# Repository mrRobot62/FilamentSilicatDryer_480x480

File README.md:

# ESP32-S3 Filament & SilicaGel Dryer UI

> English documentation is available in [README_EN.md](README_EN.md).
> Diese README ist die deutsche Hauptfassung.

## Management Summary

> [!NOTE]
>
> Große Teile der Dokumentation basieren auf aktuellen Source-Code-Ständen, Analysen und Reverse-Engineering.
> Die Formulierungen wurden zu wesentlichen Teilen KI-gestützt ausgearbeitet und werden schrittweise technisch nachgeschärft.

Technische Grundlage:

- `HOST`: ESP32-S3 mit 480x480-Touchdisplay und LVGL
- `CLIENT`: ESP32-WROOM für Aktorik, Telemetrie und Safety-Gating
- Kommunikation: UART/TTL mit ASCII-Protokoll
- Temperaturmessung: externer Thermofühler plus clientseitige Sensorik

Der Filament- und SilicaGel-Dryer ersetzt die originale Bedien- und Steuerlogik eines Mini-Backofens durch eine transparente Zwei-Controller-Architektur. Ziel ist kein kosmetischer Umbau, sondern ein nachvollziehbares, wartbares und erweiterbares Trocknungssystem für Filament und Silicagel.

## Aktueller Release-Stand

- Version: `0.7.3`
- Fokus:
  - konfigurierbarer Parameterscreen auf dem `HOST`
  - NVM-persistente Fast-Shortcuts
  - konfigurierbare Heater-Curve-Presets
  - Display-Timeout mit Dimmung und Wake-on-Touch-Schutz
  - hostseitige Langzeit-CSV-Aggregation `CSV_LR_HOST`
  - erweiterte aktive Hardware-, Wiring- und BOM-Baseline in der Doku

## Kritische Sicherheitsregel

> [!WARNING]
>
> **USB darf nicht angeschlossen werden, waehrend das Geraet am 230-V-Netz betrieben wird.**
> Durch netzseitige Bezuege des wiederverwendeten Powerboards koennen gefaehrliche Potentialunterschiede entstehen.

Erlaubte Varianten:

- Netzstecker ziehen, bevor USB verbunden wird
- USB-Isolator verwenden
- galvanisch getrennte Versorgung / isoliertes Setup verwenden

Die gepflegte Fassung dieser Regeln liegt in [doc/03_user_guide/01_installation_and_safety.md](doc/03_user_guide/01_installation_and_safety.md).

## Dokumentationsstatus

Aktiv gepflegt:

- Hardware- und Reverse-Engineering-Grundlagen
- Softwarearchitektur fuer `HOST`, `CLIENT` und Kommunikation
- Installations- und Sicherheitsbasis
- Bedienkonzept und Screen-Ueberblick
- Release- und Update-Baseline

Noch im Ausbau:

- vollstaendige Wiring-Dokumentation
- BOM mit Varianten
- Test- und Validierungsnachweise
- bebilderte Installationsschritte

## Einstieg

- Dokumentationsindex: [doc/README.md](doc/README.md)
- Hardware: [doc/01_reverse_engineering_and_hardware/README.md](doc/01_reverse_engineering_and_hardware/README.md)
- Hardware-Setup: [doc/01_reverse_engineering_and_hardware/04_hardware_setup.md](doc/01_reverse_engineering_and_hardware/04_hardware_setup.md)
- Wiring-Baseline: [doc/01_reverse_engineering_and_hardware/05_wiring_baseline.md](doc/01_reverse_engineering_and_hardware/05_wiring_baseline.md)
- BOM-Baseline: [doc/01_reverse_engineering_and_hardware/06_bom_baseline.md](doc/01_reverse_engineering_and_hardware/06_bom_baseline.md)
- Softwarearchitektur: [doc/02_software_architecture/README.md](doc/02_software_architecture/README.md)
- User Guide: [doc/03_user_guide/README.md](doc/03_user_guide/README.md)
- Installation und Sicherheit: [doc/03_user_guide/01_installation_and_safety.md](doc/03_user_guide/01_installation_and_safety.md)
- Betrieb und Screens: [doc/03_user_guide/02_operation_and_screens.md](doc/03_user_guide/02_operation_and_screens.md)
- Release und Update: [doc/03_user_guide/03_release_and_update.md](doc/03_user_guide/03_release_and_update.md)

## Referenzplattform

Aktuelle Basis:

- EMPHSISM AFTO-1505D Mini-Backofen / Airfryer
- reverse-engineertes Powerboard wird weiterverwendet
- Original-UI wird durch `HOST` und `CLIENT` ersetzt

Die aktive Hardware-Dokumentation liegt unter [doc/01_reverse_engineering_and_hardware/README.md](doc/01_reverse_engineering_and_hardware/README.md).

## Systemarchitektur

Zentrales Prinzip: `Oven Runtime State` als Single Source of Truth.

```mermaid
flowchart LR

  subgraph UX["UX Controller (ESP32 S3)"]
    S3["ESP32 S3 MCU"]
    TFT["480x480 Touch Display"]
    TOUCH["Touch Controller"]
    IO["GPIO Outputs"]
  end

  subgraph CLIENT["IO Controller (ESP32 WROOM)"]
    WROOM["ESP32 WROOM MCU"]
    UART2["UART TTL Interface"]
    OUT["Output Mask"]
    IN["Status Inputs"]
  end

  subgraph PWR["Powerboard (Reverse Engineered)"]
    PB["Powerboard Logic"]
    REL["Relays and Power Drivers"]
    SNS["Door and Safety Signals"]
  end

  subgraph SENS["External Temperature Sensor"]
    TC["Temperature Sensor"]
    AMP["Sensor Interface"]
  end

  S3 -->|"SPI or RGB"| TFT
  S3 -->|"I2C or SPI"| TOUCH
  S3 <-->|"UART TTL"| UART2
  UART2 <-->|"Serial Link"| WROOM
  WROOM -->|"Control Lines"| OUT
  OUT --> PB
  PB --> REL
  PB -->|"Status Bits"| IN
  IN --> WROOM
  TC --> AMP
  AMP --> S3
```

Die detaillierte Architektur ist unter [doc/02_software_architecture/README.md](doc/02_software_architecture/README.md) beschrieben.

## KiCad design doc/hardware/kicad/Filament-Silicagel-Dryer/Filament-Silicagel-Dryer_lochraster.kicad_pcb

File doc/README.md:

# Documentation

This folder reflects the active documentation baseline on top of release `v0.7.3`.

The active documentation is intentionally reduced to three maintained sections:

1. [Reverse Engineering and Hardware](01_reverse_engineering_and_hardware/README.md)
2. [Software Architecture](02_software_architecture/README.md)
3. [User Guide](03_user_guide/README.md)

Legacy material is still available in the archive:

- [Archive snapshot before the reorganization](archive/pre_reorg_v0.7.1/README.md)

## Scope of the active documentation

The new structure reflects the current product split:

- `HOST`: ESP32-S3 UI controller with LVGL, runtime state, parameter storage and communication control
- `CLIENT`: ESP32-WROOM hardware controller for outputs, telemetry and safety gating
- Reverse-engineered oven power board reused as actuator and supply stage

## Recommended next additions

The active structure now covers the current architecture, user operation, installation baseline and release/update baseline.

The next useful additions should be:

- a dedicated manufacturing and wiring guide
- a test and validation section
- a BOM with validated hardware variants
- an explicit safety concept and validation chapter

## Phase-2 hardware documentation status

The active hardware section now also includes:

- a hardware setup baseline
- a wiring baseline
- a BOM baseline

These pages intentionally establish the maintained structure first. They should be refined with real photos, exact connector mappings and validated part numbers in the next iterations.

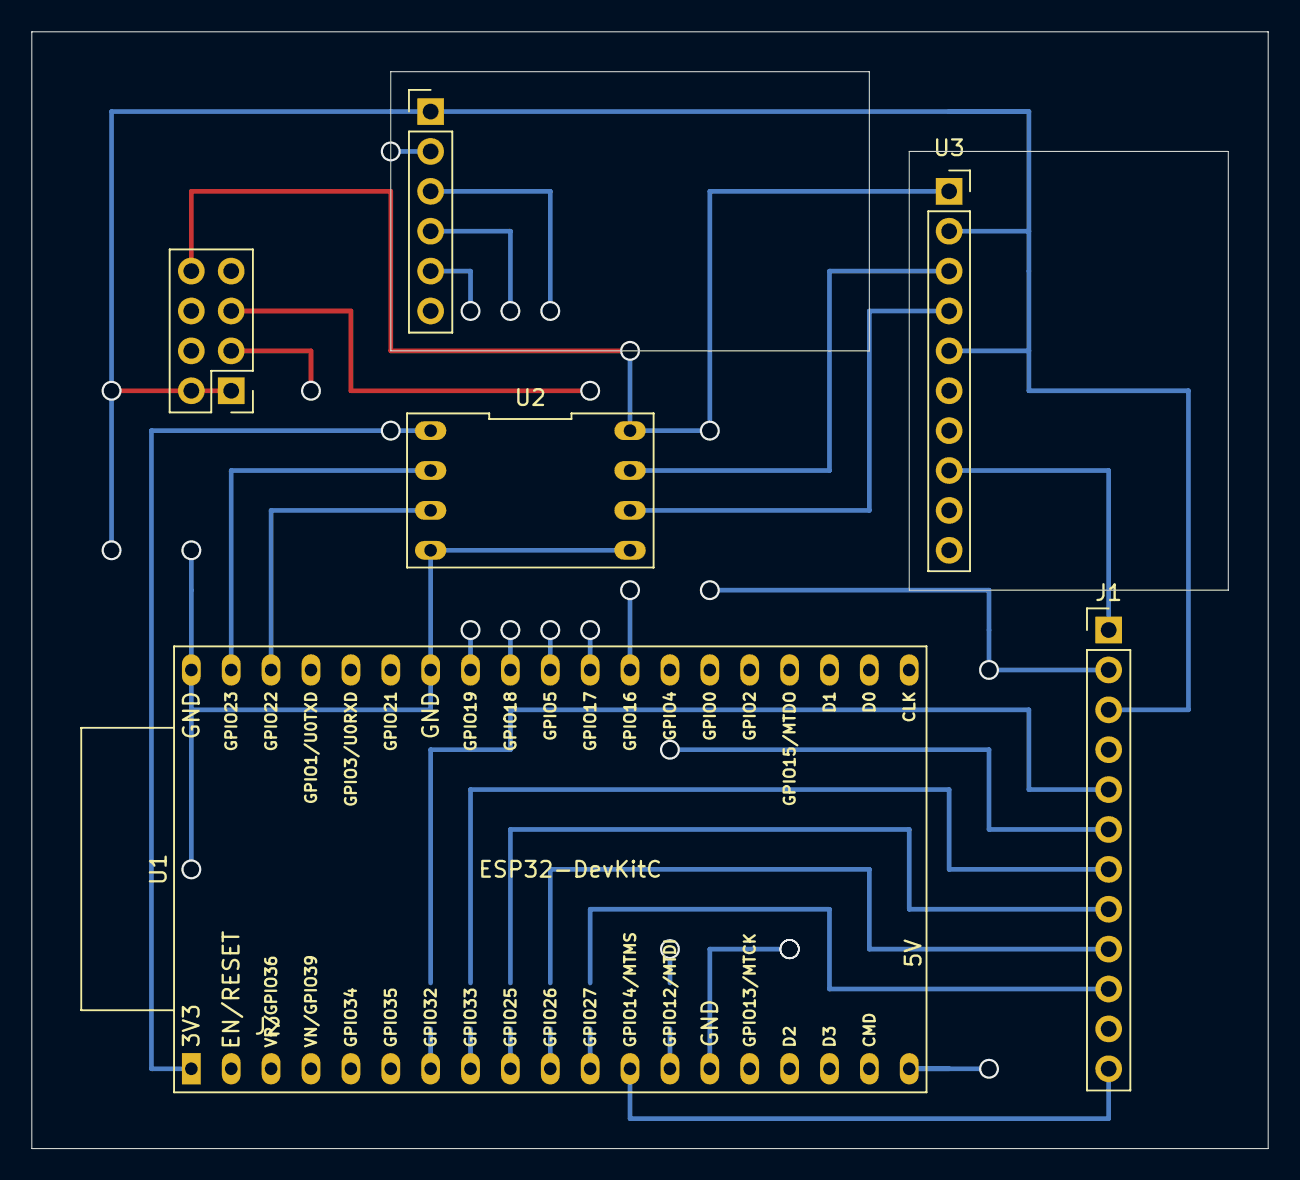
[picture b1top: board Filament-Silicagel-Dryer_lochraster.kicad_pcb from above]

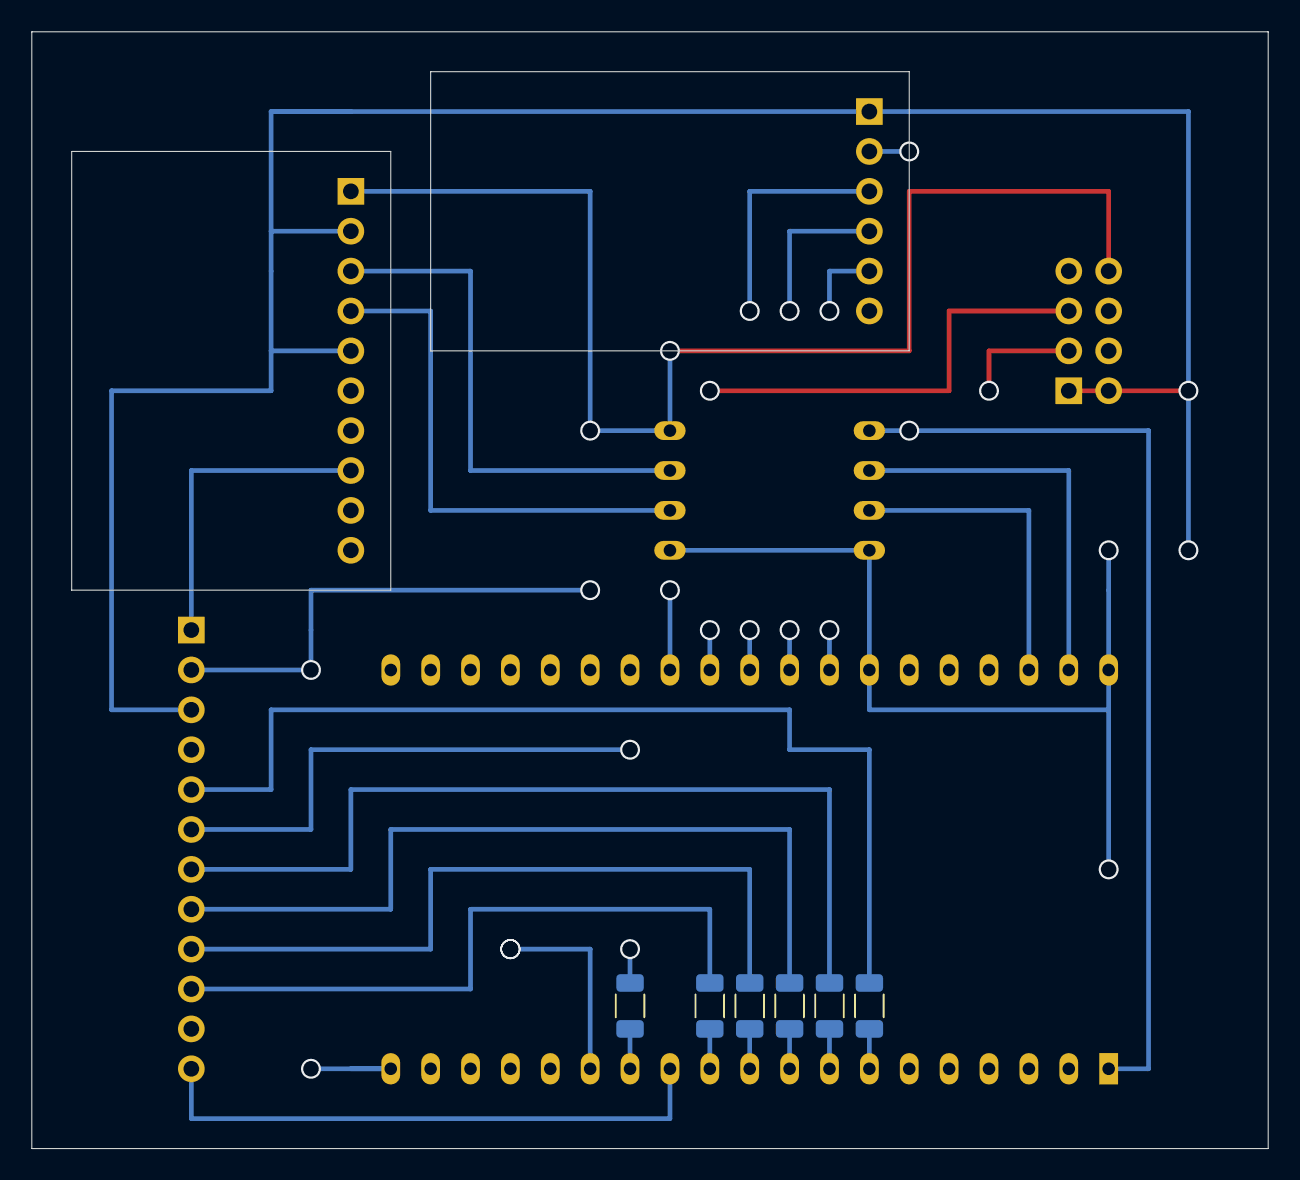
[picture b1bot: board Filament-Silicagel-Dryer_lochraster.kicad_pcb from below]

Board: 4 copper layers, 78.7 x 71.1 mm, 12 parts (6 on the bottom side), 27 nets.

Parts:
J1: Board-Connector 12Pin; PinHeader_1x12_P2.54mm_Vertical
J2: Conn_ESP32-S3; PinHeader_2x04_P2.54mm_Vertical
J3: MAX6675; PinHeader_1x06_P2.54mm_Vertical
R1, R2, R3, R4, R5, R6: 220; R_1206_3216Metric
U1: ESP32-DevKitC
U2: LevelShifter_8pin_12.7mm
U3: ADS1115_I2C_Shield; PinSocket_1x10_P2.54mm_Vertical

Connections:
CS: J3.3 (CS), U1.29 (GPIO5)
DOOR: J1.12, U1.12 (MTMS/GPIO14/ADC2_CH6)
FAN12V: J1.5, R1.1
FAN230V: J1.7, R2.1
FAN230V_SLOW: J1.10, R6.2
GND: J1.3, J2.1, J2.2, J3.1 (GND), U1.14 (GND), U1.32 (GND), U1.38 (GND), U2.4 (GND), U2.5 (GND), U3.2 (GND), U3.5 (ADDR)
HEATER: J1.6, R3.1
INT_TEMPSENSOR: J1.1, U3.7 (AIN0)
LAMP230V: J1.8, R4.2
MOTOR230V: J1.9, R5.2
NC: J1.4, J1.11
unnamed: R2.2, U1.8 (32K_XN/GPIO33/ADC1_CH5)
unnamed: R1.2, U1.7 (32K_XP/GPIO32/ADC1_CH4)
unnamed: R6.1, U1.11 (ADC2_CH7/GPIO27)
unnamed: R4.1, U1.9 (DAC_1/ADC2_CH8/GPIO25)
unnamed: R5.1, U1.10 (DAC_2/ADC2_CH9/GPIO26)
unnamed: R3.2, U1.13 (MTDI/GPIO12/ADC2_CH5)
RX2: J2.3, U1.27 (GPIO16)
SCK: J3.4 (SCK), U1.30 (GPIO18)
SCL_H: U2.7 (5A), U3.3 (SCL)
SCL_L: U1.37 (GPIO23), U2.2 (3A)
SDA_H: U2.6 (5B), U3.4 (SDA)
SDA_L: U1.36 (GPIO22), U2.3 (3B)
SO: J3.5 (SO), U1.31 (GPIO19)
TX2: J2.5, U1.28 (GPIO17)
VCC: J1.2, J2.8, U1.19 (5V), U2.8 (VIN)
VDD: J3.2 (+5V), U1.1 (3V3), U2.1 (3.3v)

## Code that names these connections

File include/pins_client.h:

#pragma once
#include <Arduino.h>

// -------------------------------------------
// Example GPIO pins (REPLACE with real pins)
// -------------------------------------------
constexpr int PIN_CH0 = 32; // GPIO32
constexpr int PIN_CH1 = 33; // GPIO33
constexpr int PIN_CH2 = 25; // GPIO25
constexpr int PIN_CH3 = 26; // GPIO26
constexpr int PIN_CH4 = 27; // GPIO27
constexpr int PIN_CH5 = 14; // GPIO14
constexpr int PIN_CH6 = 12; // GPIO12
constexpr int PIN_CH7 = 13; // GPIO13

constexpr int PIN_CH8 = 04;  // GPIO04
constexpr int PIN_CH9 = 0;   // GPIO0
constexpr int PIN_CH10 = 2;  // GPIO2
constexpr int PIN_CH11 = 15; // GPIO15

// -------------------------------------------
// Analog input pins (FOR CH12–CH15)
// -------------------------------------------
constexpr int PIN_ADC0 = 36; // ADC0
constexpr int PIN_ADC1 = 39; // ADC3
constexpr int PIN_ADC2 = 34; // ADC6
constexpr int PIN_ADC3 = 35; // ADC7

// -------------------------------------------
// MAX6675 thermocouple pins (example)
// -------------------------------------------
constexpr int PIN_MAX6675_SCK = 18; // GPIO18 (SPI_SCK)
constexpr int PIN_MAX6675_CS = 5;   // GPIO5 (SPI_SS)
constexpr int PIN_MAX6675_SO = 19;  // GPIO19 (SPI(MISO))

// -------------------------------------------
// Internel Board-LED
// -------------------------------------------
constexpr int PIN_BOARD_LED = 2;

// -------------------------------------------
// HOST-Mapping GPIO -> Logische Namen
// -------------------------------------------
constexpr int OVEN_FAN12V = PIN_CH0;
constexpr int OVEN_FAN230V = PIN_CH1;
constexpr int OVEN_FAN230V_SLOW = PIN_CH4;
constexpr int OVEN_LAMP = PIN_CH2;
constexpr int OVEN_SILICAT_MOTOR = PIN_CH3;
constexpr int OVEN_DOOR_SENSOR = PIN_CH5;
constexpr int OVEN_HEATER = PIN_CH6;

// ADC-Input
constexpr int OVEN_TEMP1_PORT1 = PIN_ADC0;
constexpr int OVEN_TEMP_KTYPE = PIN_ADC1;

// IMPORTANT: You stated that it must be initialized with RX2/TX2 routing, otherwise it won't work.
constexpr uint8_t CLIENT_RX2 = 16; // GPIO16 = RX2
constexpr uint8_t CLIENT_TX2 = 17; // GPIO17 = TX2

// EOF

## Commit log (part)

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2025-11-24 initial
2025-11-25 gfx funktioniert, lvgl noch überhaupt nicht genutzt.
2025-11-27 gfx ok, lvg 9.4.0 ok, Serial ok, "Hello LVGL 9 on ST7701"
2025-11-29 nightly
2025-12-01 update an struktur, icons.png und c files erstellt. Grundsätzlich kompilierbar
2025-12-03 Bereinigungen, rudimentärer main-screen touch funktioniert callbacks auch
2025-12-03 Bereinigungen, rudimentärer main-screen
2025-12-06 src-folder struct auf src/app und src/test angepasst. platformio.ini erweitert für src/test/i2c test und weitere tests-module. Compiliert und flash. Darstelleung in ordnung ohne Zeiger. ButtonEvent o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
2025-12-14 Stand T3 gespeichert....
2025-12-16 T4 - UI: introduce RUNNING/WAIT state machine, pause handling and door safety logic
    - Added explicit RunState (STOPPED/RUNNING/WAIT) to main screen logic
    - Implemented WAIT behavior with manual resume after door close
    - Countdown timer now pauses immediately on door open
    - Pause/WAIT button enablement tied to door state (safety-first)
    - Door state simulation added for UI testing without hardware
    - Unified countdown, needle and progress bar behavior
2025-12-17 - Ersetzt Linien-/Blockmarker der Temperaturanzeige durch PNG-Dreiecke für IST- und SOLL-Temperatur - Farblogik für CURRENT-Temperatur: - Blau: unter Zielbereich - Grün: innerhalb Zielbereich (± Tole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
2025-12-19 User kann FAN230 manuell einschalten, voraussetzung ist, das system ist !running
2025-12-20 swipe über alle drei Screen implementiert. screen_config und screen_log sind aber leer
2025-12-21 T5.3 - layout anpassungen
2025-12-27 screen_config übernahme der Daten in screen_main noch nicht implementiert
2025-12-27 nightly 20251227 (Update der Needles nach screen_config funktioniert noch nicht - alter codestand commited)
2026-01-06 archiv aktualisiert test_cases für host-client entwickelt und einige getestet
2026-01-07 TC12-TC16 implementiert und erfolgreich ausgeführt.
    Die Entwicklung von Testscases schließen wir hier:
    BEDENKEN:
    Alle technischen TestCases die tatsächlich Hardware schalten, dürfen nicht im EchtSystem durchgeführt werden. Dies kann zu Schäden führen
2026-01-07 Doc HostComm V0.2 Doc ClientComm V0.3 Inline docu HostComm
2026-01-08 T7 - AP 2.2 - done - compile ok allerdings konnt nicht über HW geprüft werden
2026-01-10 T17 - grundlegende lauffähigkeit zwischen HOST & CLIENT. UI-Updates ok basieren auf oven_runtime_status POST-Phase pro Preset möglich und OK UI-Updates OK
    offen:
    Im PostMode visuelle Darstellung in UI notwendig (zB. statt background GREEN (Filmament) in Blau.
    Dial-Frame von Orange in Blau
    ....
    Umfangreiche Tests noch nicht durchgeführt
2026-01-11 T7 AP 3.2 Kurz-Status (mentales Häkchen setzen) • ✅ LinkSync Rising Edge → SAFE STOP funktioniert • ✅ Alive-Timeout → SAFE STOP funktioniert • ✅ Icon wechselt korrekt (rot ↔ grün) • ✅ Log-Ausgaben je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
2026-01-11 T7 AP4.1b: Stabilize link sync / alive handling and UI state reflection
    - Separate linkSynced (handshake) from commAlive (RX freshness)
    - Mirror HostComm RX timestamps into OvenRuntimeState
    - Add safe STOP on alive-timeout and on link-sync rising edge
    - Prevent stale actuator coloring by forcing local STOP on comm loss
    - Keep UI link icon driven solely by runtimeState.linkSynced
    - Reduce log noise, keep diagnostics behind compiler flags
2026-01-11 T7 AP4.3 – POST nutzt identische Aktuator-Iconlogik wie RUNNING • Klarstellung: POST und RUNNING teilen sich bewusst dieselbe Icon-Darstellung • Keine Sonderfarben oder Overrides für POST-Modus • Mod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
2026-01-12 Mit T8 wird ein temporärer Debug-Hardware-Screen (screen_dbg_hw) eingeführt, der gezieltes manuelles Schalten einzelner Hardware-Ports zu Testzwecken erlaubt.
    Der Screen ist strikt vom produktiven Betrieb getrennt und hält die bestehende
    T7-Architektur vollständig ein (Single Source of Truth über oven.cpp).
    Wesentliche Punkte:
    - Neuer screen_dbg_hw mit Icons, Rows, Verbindungslinien und Temperaturanzeige
    - RUN-Gate als UI-Sicherheitsmechanismus (armed / disarmed)
    - Zentrale Safety-Funktion oven_force_outputs_off()
2026-01-15 erweiterte Dokumentation - es fehlt noch Bildmaterial
2026-01-15 erweiterte Dokumentation Installationsanweisung
2026-01-16 GitHub-Kompatible Docu
2026-01-19 KiCad PCB/Schaltplan hinzugefügt ESP32-Wroom Client hinzugefügt Dokumentationen erweitert
2026-01-27 Abschluß T9 Dokumentationen umsortierungen von Dateien ...
2026-01-28 T10.1.35: Fix heater PWM attach handling on client (GPIO12)
    Ensure LEDC attach result is checked before marking heater PWM as running.
    Prevent false PWM-active state and invalid ledcDetach calls.
    Fixes missing 4kHz PWM output on HEATER (GPIO12 / P6).
2026-01-28 T10.1.35: HEATER-PWM Start stabilisiert. Beim Aktivieren des Heaters wird der PWM-Output nun deterministisch „gekickt“ (Duty=0 → kurze Settling-Delay → Duty setzen), damit das 4kHz-Signal zuverlässig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
    Wenn du willst, machen wir als Nächstes T10.1.36b (Door-Safety-Gating inkl. FAN230 OFF bei DOOR OPEN, FAN230_SLOW bleibt any).
2026-01-29 T10.1.37: Sicherheits- und Übertemperatur-Fixes Host + Client
    Client:
    - Korrekte Abbildung des effektiven OutputsMask entsprechend des realen Hardware-Zustands.
    - DOOR bleibt strikt input-only (reine Telemetrie), wird niemals als Output angesteuert.
    - Autoritative Door-Safety auf dem Client:
    - DOOR OPEN erzwingt sofortiges Abschalten von HEATER, MOTOR und FAN230.
    - PWM-Heater wird hart deaktiviert (ledcDetach), inkl. konsistenter Shadow-Maske.
2026-01-30 T10.1.39.1: Overtemp-Cooling-Boost bei Host-Overtemperature implementiert. Bei Überschreiten von Target + Toleranz wird der HEATER zuverlässig abgeschaltet und zusätzlich aktiv auf schnelle Abkühlung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
2026-01-30 T10.1.39c – Konsolidierung Overtemp-Logik, Fan-Umschaltung & UI-Trennung
    Die Host-seitige Overtemperature-Behandlung wurde final konsolidiert und eindeutig
    strukturiert. Der Host ist nun alleinige Autorität für sicherheitsrelevante
    Aktuatorentscheidungen.
    - Overtemperature (cur >= target + tol):
    * HEATER wird abgeschaltet
    * FAN230V (FAST) wird aktiviert
2026-01-30 T10.1.40: fail-safe client watchdog (HOST timeout -> outputs=0, heater PWM off)
2026-01-30 10.1.41 – Fix: deterministischer PWM-Start des Heaters beim ersten START nach Boot
    Behebt einen kritischen Initialisierungsfehler im Client, bei dem der HEATER beim ersten START nach Systemboot trotz gesetztem OutputsMask kein 4 kHz-PWM-Signal erzeugt hat. Ursache war ein nicht-det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
    Der Fehler zeigte sich nur beim ersten START, während STOP → START zuverlässig funktionierte, da hierbei ein expliziter Detach/Attach-Zyklus stattfand.
    Fix:
    • PWM-Enable wurde so angepasst, dass ein deterministischer Start garantiert i
2026-02-12 T11.1 oven: add thermal model scaffold (T_ntc/T_core fields)
2026-02-13 T11.3 thermal: tune defaults + pulse gating clamps + richer debug
2026-02-13 T11.4.1 thermal: robustness clamps + coreValid gating + richer debug
2026-02-16 Highlighting umgebaut
2026-02-17 T12: UDP runtime config via Preferences + boot integration + logging fixes
    - Introduced UdpLogConfig runtime model (SSID, password, target IP, target port)
    - Added Preferences-based persistence (udp_cfg_load/save/clear)
    - Boot-time load of UDP/WiFi config (works without visiting screen_udp)
    - Runtime configuration of udp_log (IP + PORT configurable)
    - Fallback to build defaults if no Preferences present
    - Added privacy-safe boot logs (SSID + pw_len, no password content)
2026-02-19 T13 Step 3: Client dual-NTC measurement and STATUS protocol extension
    Client firmware updated to support dual NTC temperature measurement using ADS1115.
    Changes:
    - Added measurement of two independent NTC sensors:
    - CH0: tempHotspotC (safety)
    - CH1: tempChamberC (control)
    - Implemented table-based temperature conversion using iOVEO 10k NTC reference data
2026-02-19 T13 Step 4.1.0: Add safety layer and relay-safe heater control
    Implemented safety supervision and relay-safe heater control based on the new dual-NTC architecture.
    Changes:
    - Added safetyCutoffActive flag to OvenRuntimeState
    - Implemented hotspot hard cutoff using tempHotspot_dC
    - Implemented chamber fail-safe temperature limit
    - Added overshoot cap protection relative to target temperature
2026-02-19 T13 Step 4.2.0: Add safety status icon to main screen
    Integrated safety status visualization into the main UI screen.
    Changes:
    - Added safetyCutoffActive handling to screen_main
    - Introduced new safety icon in the top bar (using existing link asset as placeholder)
    - Implemented dynamic recolor:
    - Green = safety OK
2026-02-24 UDP-Patch1/3
2026-02-25 T14.0 client: implement SafetyGuard safe-state and safety latch
    - add enterSafeState_() central fail-safe handler
    - heater forced OFF on parse errors, RX overflow, HostRst, unexpected frames
    - add safety latch: heater remains OFF until explicit SET/UPD/TOG from host
    - refactor host timeout handling to use central safe-state logic
    - ensure deterministic and testable safety behaviour
2026-02-25 T14 SafetyGuard: initial implementation
2026-02-25 UDP Logfix - Testok - HOST & CLIENT UPD Log available
2026-02-25 merge
2026-02-25 T14.0 client: fix SafetyGuard state flags and header declarations
    - keep g_hostTimeoutActive consistent when entering safe state
    - clear g_hostTimeoutActive when safety latch is cleared by host command
    - add missing private declarations/members to ClientComm.h
2026-02-25 T14.0 client: add SafetyGuard reporting getters (reason/time/latched)
    - expose safety latch state and last safety reason/time for tests and app
    - add reason-to-string helper for readable logs and diagnostics
    - no protocol changes (backwards compatible)
2026-02-27 T15 Step 1: Introduce client_heater_curve test endpoint (Client-only Heater Curve Lab baseline)
    Purpose:
    Establish a minimal, standalone Client endpoint to experimentally evaluate heater control behavior
    without HostComm dependency. This endpoint will serve as a controlled environment to develop and
    validate a stable heater curve algorithm for the chamber temperature (Dual-NTC architecture).
    Key characteristics:
    - New endpoint: src/client/T15/client_heater_curve.cpp
2026-03-15 T15-S3
2026-03-15 T15-2.3: stabilize chamber-only test framework and logging before CSV extension
    Current state:
    - Chamber NTC measurement fully functional (ADS1115 CH1)
    - Hotspot channel temporarily disabled but still logged as NaN (Thot=nanC)
    - Heater curve test state-machine working:
    HEATING → RUNOUT → WAIT_FOR_COOL → NEXT RUN
    - Overshoot detection and time-to-peak measurement implemented
2026-03-22 T15 - Abschlußstand
2026-03-22 T16.Misc.1.0 introduce client sensor_ntc and heater_io interfaces (no integration yet)
2026-03-22 T16.Client.1.0 migrate real dual-NTC sensor path into client
2026-03-22 T16 integrate dual-NTC sensing, heater I/O separation and host request/actual model
    Client:
    - integrate dual-NTC sensor path (hotspot + chamber via ADS1115)
    - introduce sensor_ntc module (measurement, conversion, door handling)
    - extract heater PWM control into heater_io module (4kHz, ~50% duty, safe off)
    - remove legacy T15 dependencies from runtime path
    - add periodic diagnostic logging (state, mask, temps, heater, door)
2026-03-27 T16_Phase_1.0 remove T11 host runtime remnants
2026-03-27 T16_Phase_1.2 defer heater activation until control loop
2026-03-27 T16_Phase_1.4 isolate host safety logic and normalize versions
2026-03-27 T16_Phase_2.0 add host plot logic logging baseline
2026-03-27 T16_Phase_2.0.2 restore bracketed CSV log sources
2026-03-29 T16_Phase_2.2 add staged host heater control
2026-03-29 T16_Phase_2.3 extend host logic logging with policy stage
2026-03-29 T16_Phase_2.4 document phase 2 and hardware test plan
2026-03-29 T16_Phase_2.5.1 fix client logic bit mapping
2026-03-30 T16_Phase_3.0 add conservative filament cutoff and fast cooldown
2026-03-31 T16_Phase_3.2 add timed filament fan hysteresis
2026-03-31 T16_Phase_3.3 tune filament resume after wait
2026-03-31 T16_Phase_3.4 adapt filament wait recovery to target and duration
2026-03-31 kleinere anpassungen an log_csv.h
2026-03-31 T16_Phase_4.0 introduce preset heater curve profiles
2026-03-31 T16_Phase_4.1.1 tune silica 100C pulse timing
2026-04-02 T16_Phase_4.1.3 tune high 80C hold reheat
2026-04-02 T16_Doc_4.1 document heatercurve technology
2026-04-03 Refine main screen workflow and document screen_main
2026-04-03 Embed boot logo and animate blue frame
2026-04-03 Fix boot screen version label crash
2026-04-04 Stabilize T16 release builds
2026-04-04 Persist host parameters in NVM
2026-04-04 Apply configurable host parameters
2026-04-04 Refine parameters screen workflow
2026-04-06 Add logo assets
2026-04-06 Release 0.7.0 parameters and display timeout
2026-04-09 Align 0.7.1 fallback build id
2026-04-09 Bump version to 0.7.2
2026-04-09 Remove obsolete client backup sources
2026-04-12 Prepare 0.7.3 release
2026-04-12 Add delayed start oven runtime flow
2026-04-13 Add delayed start UI and session navigation
